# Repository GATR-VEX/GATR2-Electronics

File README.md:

# GATR2 Electronics

Sensor hardware for a VEX U robot: circuit boards, control board firmware, and
the Brain library that talks to the control board.

```
tracking wheels (TW0, TW1, TW2) --> control board --RS-485, one Smart Port--> V5 Brain
IMU board (optional) -------------^   (Pico)             VEX IMU (optional) --^
```

The control board keeps the latest reading of every sensor and sends them all
when the Brain asks. The Brain turns them into a pose (locaGATR in
GATR2-Override). Heading comes from either the [IMU board](pcb/IMU/README.md)
on the control board (not read by the firmware yet) or a VEX Inertial Sensor
on the Brain.

Host tested; not run on a control board yet.

| Folder | What |
|---|---|
| [pico/locaGATR](pico/locaGATR/README.md) | Control board firmware |
| [brain/locaGATR](brain/locaGATR/README.md) | Brain library: the link to the control board |
| [pcb/ControlBoard](pcb/ControlBoard/README.md) | Control board: Pico, three encoder connectors, IMU connector, RS-485 to one Smart Port |
| [pcb/IMU](pcb/IMU/README.md) | Optional IMU board |
| [pcb/MagneticEncoder](pcb/MagneticEncoder/README.md) | Tracking wheel encoders |
| [docs](docs/README.md) | Component names, PCB contribution guide |

## Firmware

Needs [PlatformIO](https://platformio.org/). From `pico/locaGATR`:

```sh
pio run                 # build
pio run -t upload       # flash (hold BOOTSEL the first time)
pio device monitor      # status line
```

## Host tests

CMake 3.16+ and a C++17 compiler. Windows: MSYS2 ucrt64 with
`C:\msys64\ucrt64\bin` first on PATH, and `-G "MinGW Makefiles"` on each
first command.

```sh
cmake -S pico/locaGATR/tests -B build-locagatr-board-tests
cmake --build build-locagatr-board-tests
ctest --test-dir build-locagatr-board-tests

cmake -S brain -B build-brain
cmake --build build-brain --parallel
ctest --test-dir build-brain --output-on-failure
```

## Brain library in a PROS project

Clone this repo next to the robot code and include
[brain/gatr2_brain.mk](brain/gatr2_brain.mk) from the project `Makefile`; see
the [Brain README](brain/README.md).

## Contributing

Changes reach `main` only through a PR: threads resolved, `build` passing,
up to date, one code owner approval, merged by the owner. The rules are on
GitHub under Settings, Rules.
New boards and revisions: [PCB contribution guide](docs/contributing/README.md).

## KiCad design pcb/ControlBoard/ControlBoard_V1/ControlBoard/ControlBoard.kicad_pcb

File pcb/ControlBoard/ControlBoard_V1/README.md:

# Control board V1

[Control board overview](../README.md) · [All PCBs](../../README.md)

**Status: ordered, not yet built or powered.**

Project: [ControlBoard.kicad_pro](ControlBoard/ControlBoard.kicad_pro). Sheets:
root (Pico, power), `BrainLink` (RS-485), `IMU` (IMU connector), and three
`TrackingWheel` instances.

## What is on the board

| Part | Role |
|---|---|
| Raspberry Pi Pico (`A1`), socketed on headers | Counts the encoders, reads the IMU, answers the Brain |
| THVD1400DRLR (`U1`), 3.3 V RS-485 transceiver | Half-duplex link to the Smart Port; receive by default |
| AP2112K-3.3 (`U2`) | 3.3 V for encoders, IMU and transceiver, from the 5 V rail |
| 4P4C jack (`RJ1`, Cankemeng R-RJ11R04P-A802) | V5 Smart Port: 12 V in, RS-485 A and B |
| JST PH 4-pin `BuckConverter1` | Carries 12 V out to an external 12 V to 5 V module and 5 V back |
| JST PH 4-pin `TW0`, `TW1`, `TW2` | Tracking-wheel encoders |
| JST PH 6-pin `IMU1` | [IMU v2](../../IMU/IMU_V2/README.md) over I2C |

Two copper layers, 75.1 x 42.9 mm, ground pour on both sides, 0.6 mm vias with
0.3 mm drills. All passives are 0805 (1206 for the 22 uF parts), hand-solder
footprints.

## Power

```
Smart Port pin 1 (+12 V) --> C7 22 uF, C8 1 uF --> BuckConverter1 pins 1,2 (12 V, GND)
BuckConverter1 pins 3,4 (GND, 5 V) --> +5 V rail: C12 22 uF, C13 1 uF, C1 22 uF, C2 1 uF
+5 V --> Pico VSYS (pin 39)
+5 V --> U2 AP2112K-3.3 (EN tied to VIN, C20 1 uF in, C4 1 uF out) --> +3.3 V rail
```

The 3.3 V rail from `U2` feeds the encoders, the IMU and the transceiver. The
Pico's own 3V3 output (pin 36) is left unconnected, so the Pico's logic runs
from its internal regulator and everything else from `U2`. Both are nominally
3.3 V; the GPIO levels are compatible.

The Pico's VBUS, 3V3_EN and RUN pins are unconnected. The Pico stays
programmable over its USB connector; its on-board Schottky diode sits between
VBUS and VSYS, so USB and the 5 V rail can be present at the same time.

All capacitors are rated 50 V, including the two on the 12 V input.

## Pico pin assignment

| Pico pin | GPIO | Net | Function |
|---|---|---|---|
| 1, 2 | GP0, GP1 | `TW0_A`, `TW0_B` | Encoder 0 (A/B) |
| 4, 5 | GP2, GP3 | `TW1_A`, `TW1_B` | Encoder 1 |
| 6, 7 | GP4, GP5 | `TW2_A`, `TW2_B` | Encoder 2 |
| 9 | GP6 | `IMU_SDA` | I2C1 SDA |
| 10 | GP7 | `IMU_SCL` | I2C1 SCL |
| 11 | GP8 | `INT1_ACCEL` | BMI088 accelerometer interrupt |
| 12 | GP9 | `INT3_GYRO` | BMI088 gyroscope interrupt |
| 15 | GP11 | `EN` | RS-485 driver enable (DE and /RE), 10 k pulldown |
| 16 | GP12 | `RSTX` | UART0 TX to transceiver D |
| 17 | GP13 | `RSRX` | UART0 RX from transceiver R |
| 39 | VSYS | `+5V` | Supply |
| 3, 8, 13, 18, 23, 28, 38 | GND | `GND` | |

Free for later use: GP10, GP14 to GP22, GP26 to GP28 (ADC), RUN, VBUS, 3V3_EN.

## Connectors

Pin 1 is the square pad on every JST footprint.

| Connector | Pin 1 | Pin 2 | Pin 3 | Pin 4 | Pin 5 | Pin 6 |
|---|---|---|---|---|---|---|
| `TW0`, `TW1`, `TW2` (PH 4) | +3.3 V | A | B | GND | | |
| `IMU1` (PH 6) | +3.3 V | SDA | SCL | GYRO_INT | ACCEL_INT | GND |
| `BuckConverter1` (PH 4) | +12 V | GND | GND | +5 V | | |
| `RJ1` Smart Port (4P4C) | +12 V | GND | B | A | | |

`IMU1` matches `J1` on IMU v2 pin for pin, so the cable is a straight 1:1
JST PH lead. The I2C pull-ups live on the IMU board, not here.

Each encoder input has a 100 ohm series resistor at the connector and a 10 k
pulldown at the Pico, and each encoder connector has a 1 uF capacitor on its
3.3 V pin. The IMU connector has 1 uF and 0.1 uF on 3.3 V.

The Smart Port pin order was checked against a real cable by the designer. The
RS-485 direction (which of A and B the Brain treats as non-inverting) has not
been verified; if the first bench test shows garbage at the right baud, swap A
and B at the jack.

## RS-485 link

`U1` runs from 3.3 V with 1 uF decoupling. `DE` and `/RE` are tied together on
`EN` (GP11) with a 10 k pulldown, so the transceiver listens whenever the Pico
is not driving the pin, including during boot and when the firmware has not
started. The firmware then holds `EN` high: the board streams its readings and
the Brain never transmits ([protocol](../../../docs/protocol.md)).

There is no termination or bias network on A and B. The THVD1400 has an
internal receiver fail-safe for open, shorted and idle buses, and the Smart
Port cable is short, so this is acceptable for a first build. A footprint for
an optional 120 ohm termination across A and B would cost nothing and may help
if the first bench test shows reflections at the baud rate finally chosen.

## Not yet verified on hardware

- Smart Port RS-485 polarity and the Brain's turnaround timing, as noted above.
- The 12 V to 5 V module's start-up behaviour on the Smart Port's current
  limit. The port supplies 12 V through the Brain's own protection; the module's
  inrush with 2 x 22 uF plus its own input capacitance has not been measured.
- Encoder signal integrity through the 100 ohm series resistors at the counting
  rate of the fastest wheel.

## For the next revision

- Pico at the board edge, USB connector overhanging, so the cable goes in
  straight without levering the Pico in its socket.
- A diode (Schottky, or an ideal diode such as the LM66100) between the buck
  output and VSYS. On V1, USB alone back-feeds the 5 V rail into the buck
  module, so the buck has to be unplugged when only USB is connected.
- LEDs on the 12 V and 3.3 V rails.
- A TVS on the Smart Port +12 V pin.

## Files

- [KiCad project](ControlBoard/ControlBoard.kicad_pro), [root schematic](ControlBoard/ControlBoard.kicad_sch),
  [RS-485 sheet](ControlBoard/RS-485.kicad_sch), [IMU sheet](ControlBoard/BMI088_Connector.kicad_sch),
  [tracking wheel sheet](ControlBoard/TrackingWheel.kicad_sch), [layout](ControlBoard/ControlBoard.kicad_pcb)
- Custom footprint: `VexPorts:VexPort` (the 4P4C jack) in
  [ControlBoard/VexPorts.pretty/](ControlBoard/VexPorts.pretty/), referenced
  from the project's `fp-lib-table`. [VEX-Port-Footprint/](VEX-Port-Footprint/)
  holds the easyeda2kicad import it was derived from, with the symbol and the
  STEP and WRL models; it is not in the library table, which is why ERC warns
  about a missing `easyeda2kicad` library on one symbol

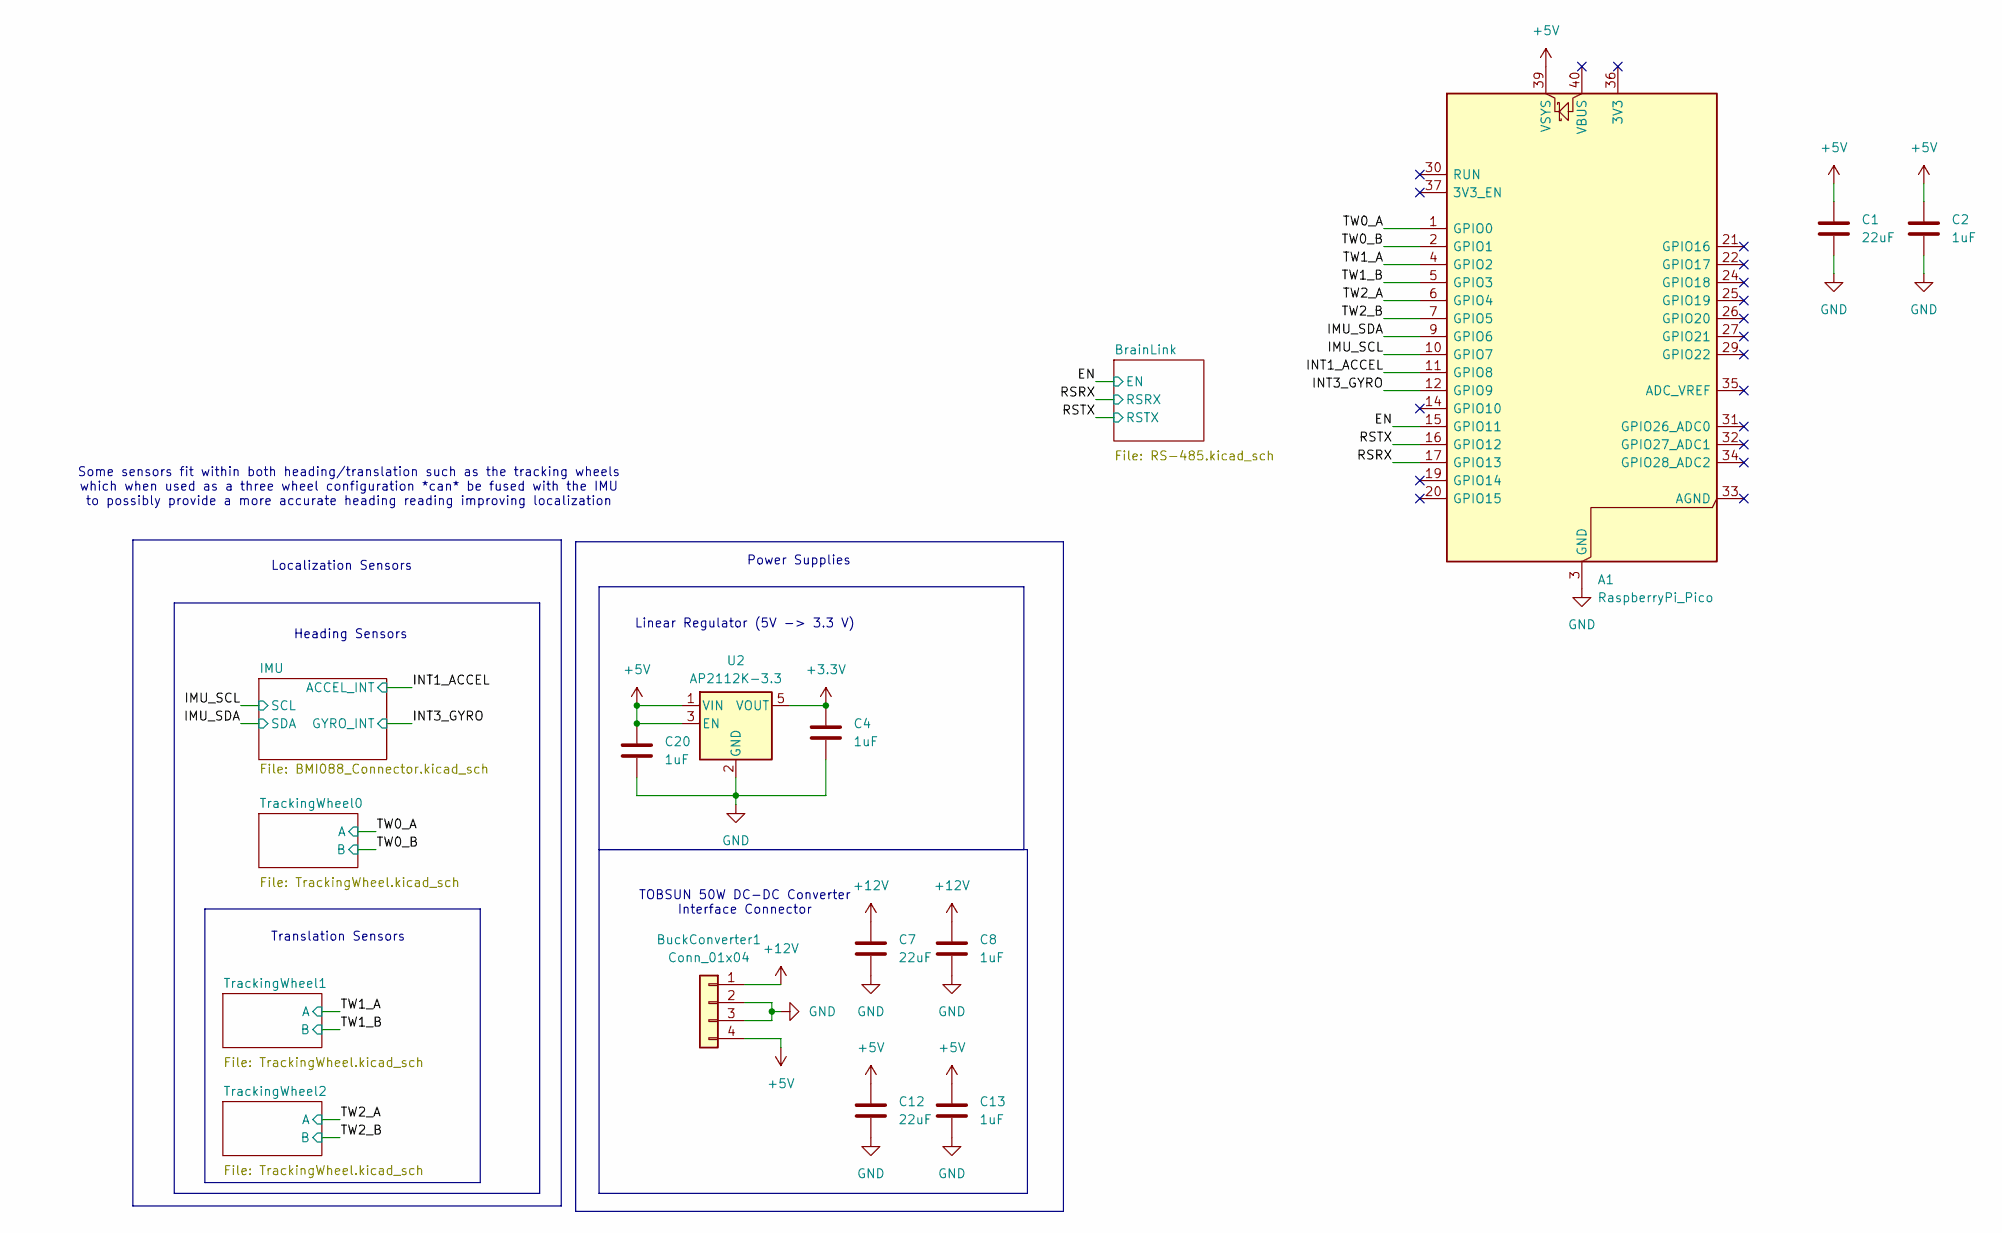
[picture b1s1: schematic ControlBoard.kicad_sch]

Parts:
A1: RaspberryPi_Pico; RaspberryPi_Pico_Common_Unspecified
BuckConverter1: Conn_01x04; JST_PH_S4B-PH-K_1x04_P2.00mm_Horizontal
C1, C7, C12: 22uF; C_1206_3216Metric_Pad1.33x1.80mm_HandSolder
C2, C4, C8, C13, C20: 1uF; C_0805_2012Metric_Pad1.18x1.45mm_HandSolder
U2: AP2112K-3.3; SOT-23-5

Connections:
+3.3V: C4.1, U2.5 (VOUT); also elsewhere on the board
+5V: A1.39 (VSYS), BuckConverter1.4, C1.1, C2.1, C12.1, C13.1, C20.1, U2.1 (VIN), U2.3 (EN)
+12V: BuckConverter1.1, C7.1, C8.1; also elsewhere on the board
/EN: A1.15 (GPIO11); also elsewhere on the board
/IMU_SCL: A1.10 (GPIO7); also elsewhere on the board
/IMU_SDA: A1.9 (GPIO6); also elsewhere on the board
/INT1_ACCEL: A1.11 (GPIO8); also elsewhere on the board
/INT3_GYRO: A1.12 (GPIO9); also elsewhere on the board
/RSRX: A1.17 (GPIO13); also elsewhere on the board
/RSTX: A1.16 (GPIO12); also elsewhere on the board
/TW0_A: A1.1 (GPIO0); also elsewhere on the board
/TW0_B: A1.2 (GPIO1); also elsewhere on the board
/TW1_A: A1.4 (GPIO2); also elsewhere on the board
/TW1_B: A1.5 (GPIO3); also elsewhere on the board
/TW2_A: A1.6 (GPIO4); also elsewhere on the board
/TW2_B: A1.7 (GPIO5); also elsewhere on the board
GND: A1.3 (GND), A1.8 (GND), A1.13 (GND), A1.18 (GND), A1.23 (GND), A1.28 (GND), A1.38 (GND), BuckConverter1.2, BuckConverter1.3, C1.2, C2.2, C4.2, C7.2, C8.2, C12.2, C13.2, C20.2, U2.2 (GND); also elsewhere on the board

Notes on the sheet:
Power Supplies
Heading Sensors
Translation Sensors
TOBSUN 50W DC-DC Converter Interface Connector
Linear Regulator (5V -> 3.3 V)
Localization Sensors
Some sensors fit within both heading/translation such as the tracking wheels which when used as a three wheel configuration *can* be fused with the IMU to possibly provide a more accurate heading reading improving localization

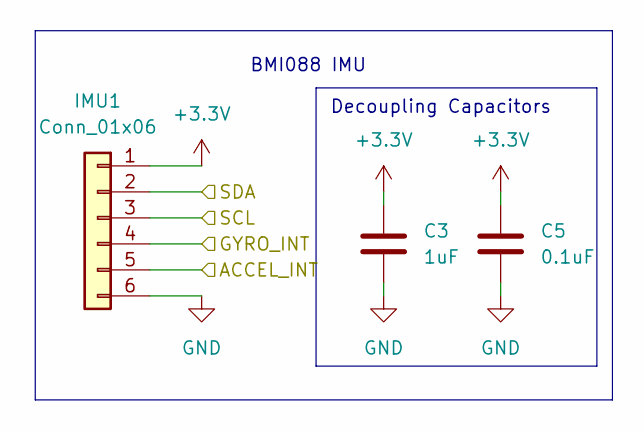
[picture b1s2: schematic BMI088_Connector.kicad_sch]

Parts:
C3: 1uF; C_0805_2012Metric_Pad1.18x1.45mm_HandSolder
C5: 0.1uF; C_0805_2012Metric_Pad1.18x1.45mm_HandSolder
IMU1: Conn_01x06; JST_PH_S6B-PH-K_1x06_P2.00mm_Horizontal

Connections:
+3.3V: C3.1, C5.1, IMU1.1; also elsewhere on the board
/IMU_SCL: IMU1.3; also elsewhere on the board
/IMU_SDA: IMU1.2; also elsewhere on the board
/INT1_ACCEL: IMU1.5; also elsewhere on the board
/INT3_GYRO: IMU1.4; also elsewhere on the board
GND: C3.2, C5.2, IMU1.6; also elsewhere on the board

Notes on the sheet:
Decoupling Capacitors
BMI088 IMU

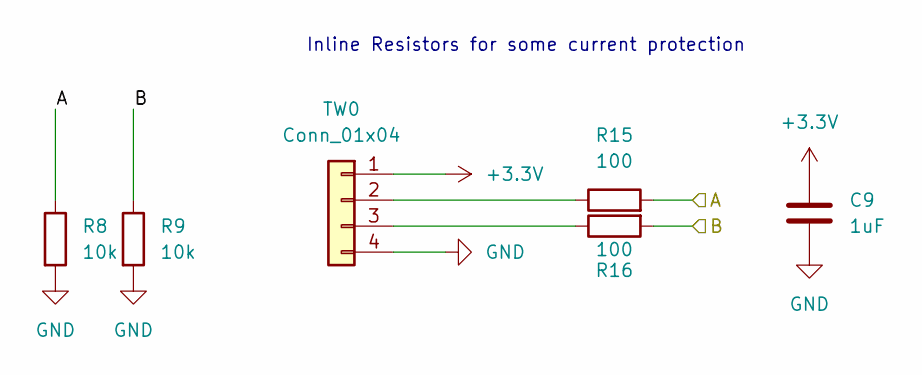
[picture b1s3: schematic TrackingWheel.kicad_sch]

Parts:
C9: 1uF; C_0805_2012Metric_Pad1.18x1.45mm_HandSolder
R8, R9: 10k; R_0805_2012Metric_Pad1.20x1.40mm_HandSolder
R15, R16: 100; R_0805_2012Metric_Pad1.20x1.40mm_HandSolder
TW0: Conn_01x04; JST_PH_S4B-PH-K_1x04_P2.00mm_Horizontal

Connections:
+3.3V: C9.1, TW0.1; also elsewhere on the board
/TW0_A: R8.1, R15.2; also elsewhere on the board
/TW0_B: R9.1, R16.2; also elsewhere on the board
GND: C9.2, R8.2, R9.2, TW0.4; also elsewhere on the board
unnamed: R15.1, TW0.2
unnamed: R16.1, TW0.3

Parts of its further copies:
C10, C11: 1uF; C_0805_2012Metric_Pad1.18x1.45mm_HandSolder
R10, R11, R12, R13: 10k; R_0805_2012Metric_Pad1.20x1.40mm_HandSolder
R17, R18, R19, R20: 100; R_0805_2012Metric_Pad1.20x1.40mm_HandSolder
TW1, TW2: Conn_01x04; JST_PH_S4B-PH-K_1x04_P2.00mm_Horizontal

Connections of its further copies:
+3.3V: C10.1, C11.1, TW1.1, TW2.1; also elsewhere on the board
/TW1_A: R10.1, R17.2; also elsewhere on the board
/TW1_B: R11.1, R18.2; also elsewhere on the board
/TW2_A: R12.1, R19.2; also elsewhere on the board
/TW2_B: R13.1, R20.2; also elsewhere on the board
GND: C10.2, C11.2, R10.2, R11.2, R12.2, R13.2, TW1.4, TW2.4; also elsewhere on the board
unnamed: R17.1, TW1.2
unnamed: R18.1, TW1.3
unnamed: R19.1, TW2.2
unnamed: R20.1, TW2.3

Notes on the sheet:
Inline Resistors for some current protection

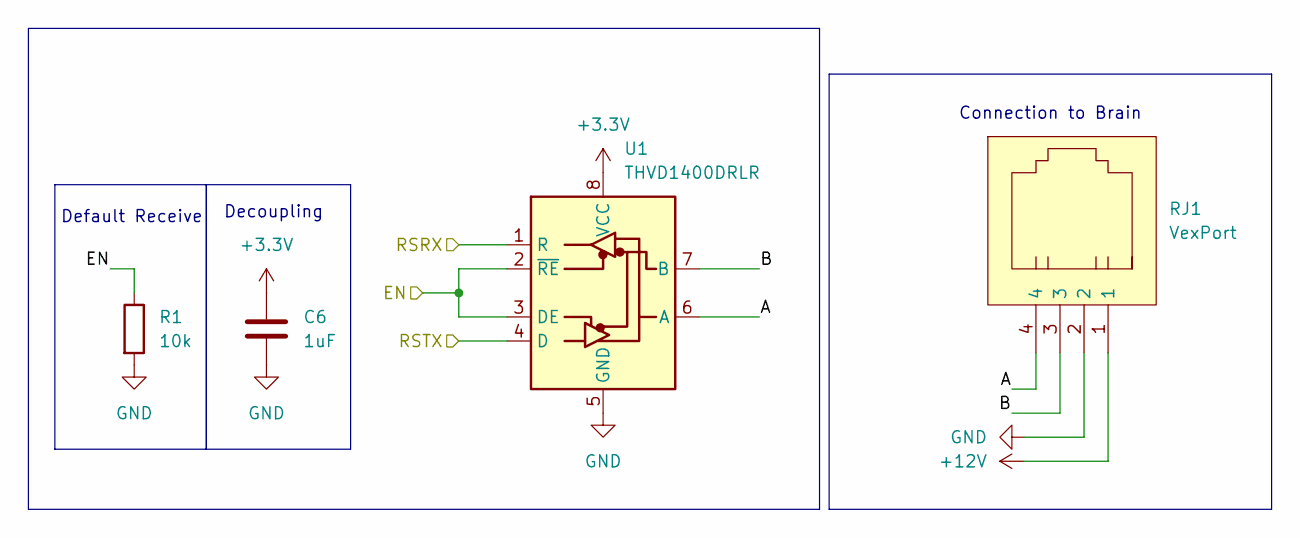
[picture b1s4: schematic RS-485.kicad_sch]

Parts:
C6: 1uF; C_0805_2012Metric_Pad1.18x1.45mm_HandSolder
R1: 10k; R_0805_2012Metric_Pad1.20x1.40mm_HandSolder
RJ1: VexPort; MPN R-RJ11R04P-A802; LCSC Part C189737
U1: THVD1400DRLR; SOT-583-8

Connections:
+3.3V: C6.1, U1.8 (VCC); also elsewhere on the board
+12V: RJ1.1; also elsewhere on the board
/BrainLink/A: RJ1.4, U1.6 (A)
/BrainLink/B: RJ1.3, U1.7 (B)
/EN: R1.1, U1.2 (~RE), U1.3 (DE); also elsewhere on the board
/RSRX: U1.1 (R); also elsewhere on the board
/RSTX: U1.4 (D); also elsewhere on the board
GND: C6.2, R1.2, RJ1.2, U1.5 (GND); also elsewhere on the board

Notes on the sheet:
Default Receive
Decoupling
Connection to Brain

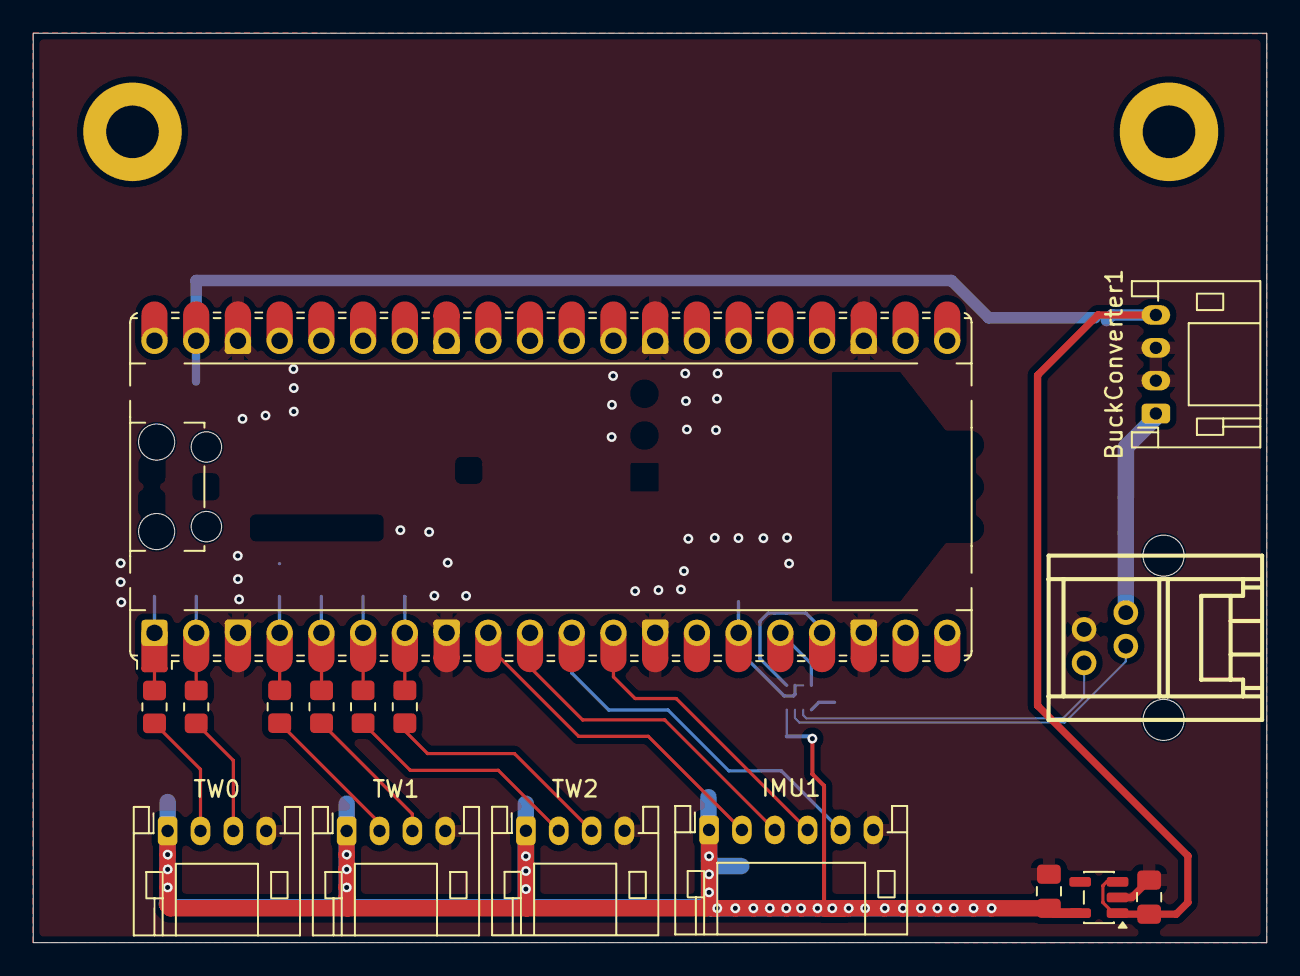
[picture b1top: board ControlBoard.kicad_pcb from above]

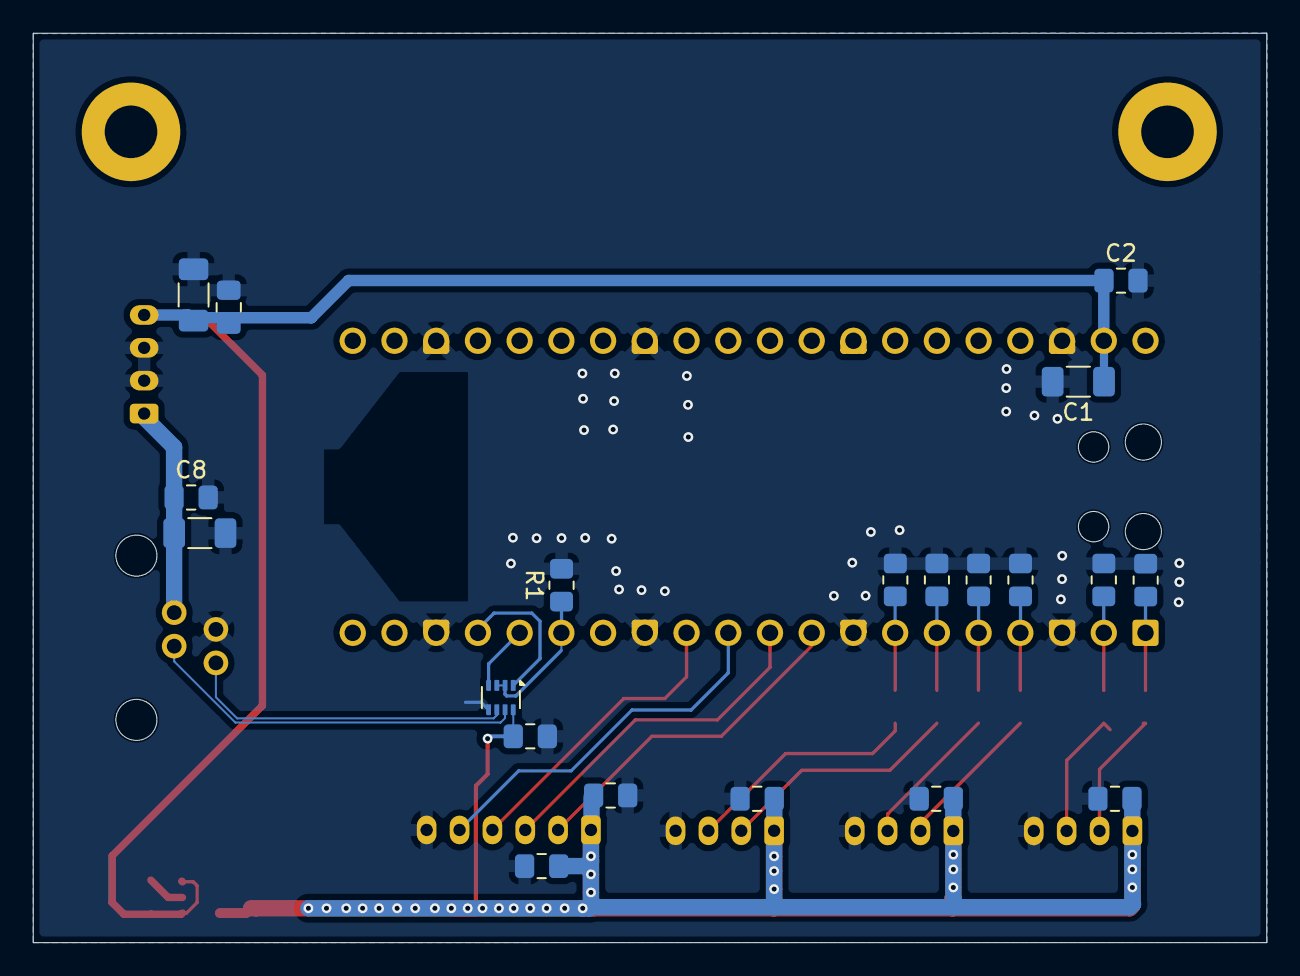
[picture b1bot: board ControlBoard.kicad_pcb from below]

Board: 2 copper layers, 75.1 x 55.4 mm, 36 parts (20 on the bottom side), 25 nets.
